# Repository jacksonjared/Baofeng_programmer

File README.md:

# Baofeng Programming Adapter

This board adapts the 5 volt USB port from a computer to 3V3 UART for use with programming Baofeng or similar chinese HTs. Most of these radios use a "Kenwood style" connector for programming; I have chosen to use separate 3.5mm and 2.5mm jacks as, annoyingly, several of the brands use non-standard spacing so as to make most cable incompatible. I have also elected to use a Silicon Labs chip to avoid the driver fiasco with the other common supplier of cheap UART bridge ICs.

## 3d

Within the folder labled '3d', you will find a .step file of the complete board and all its components, as well as models for the non-standard parts I used. I made a casing for this board to be 3D printed, but I currently do not have that file on hand. If I get a copy of it again sometime in the future, I will add it.

## gerber.zip

This is an archive of all the gerber files needed for manufacturing. I did not bother having this assembled in the factory so there is no BOM or pick-and-place file.

## main_board

I originally made this board in Kicad 5, and have since updated it to Kicad 6. I do not see anything obviously wrong with the project after converting, but I have not looked that close. If I notice any problems, I will fix them and push the change.

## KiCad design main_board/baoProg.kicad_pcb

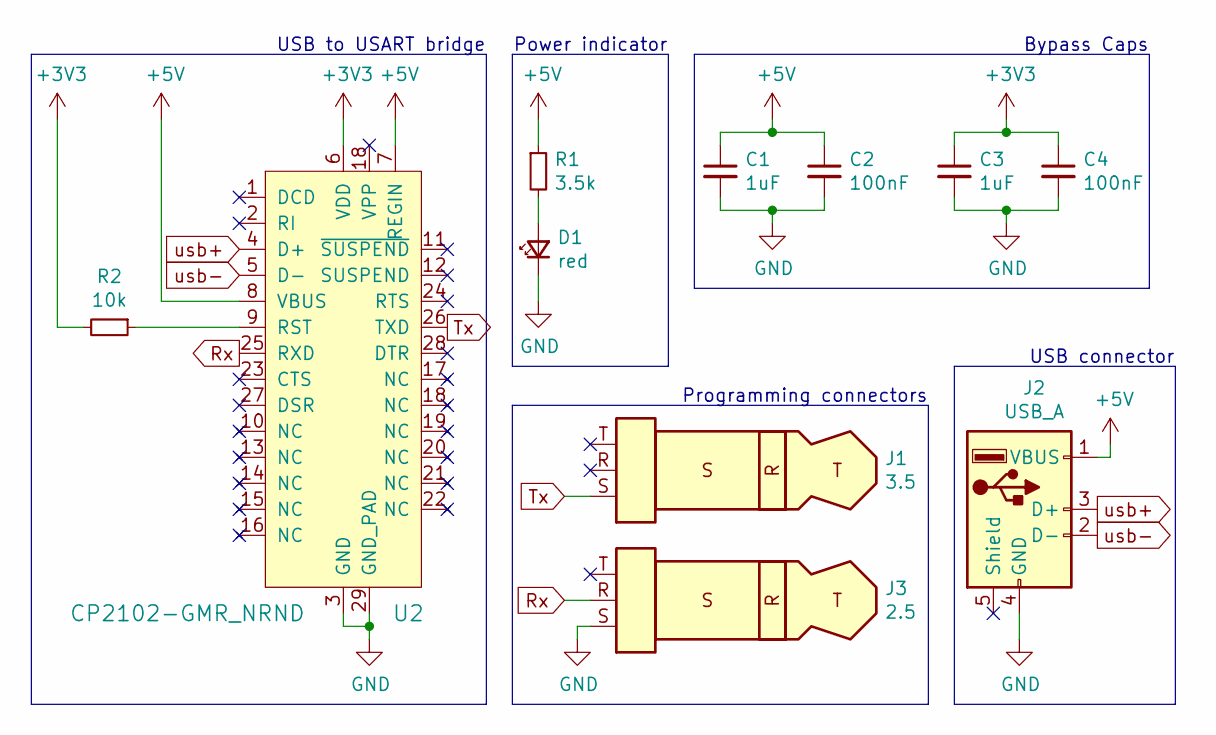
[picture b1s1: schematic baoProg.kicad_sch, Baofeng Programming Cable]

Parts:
C1, C3: 1uF; C_0603_1608Metric_Pad1.08x0.95mm_HandSolder
C2, C4: 100nF; C_0603_1608Metric_Pad1.08x0.95mm_HandSolder
D1: red; LED_0603_1608Metric_Castellated
J1: 3.5; STX-3000
J2: USB_A; USB_A_CNCTech_1001-011-01101_Horizontal_3d
J3: 2.5; STX-2000
R1: 3.5k; R_0805_2012Metric_Pad1.20x1.40mm_HandSolder
R2: 10k; R_0805_2012Metric_Pad1.20x1.40mm_HandSolder
U2: CP2102-GMR_NRND; QFN-28-1EP_5x5mm_P0.5mm_EP3.35x3.35mm_ThermalVias; MPN CP2102-GMR; Digi-Key_PN 336-1160-1-ND

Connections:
+3V3: C3.1, C4.1, R2.2, U2.6 (VDD)
+5V: C1.1, C2.1, J2.1 (VBUS), R1.1, U2.7 (REGIN), U2.8 (VBUS)
GND: C1.2, C2.2, C3.2, C4.2, D1.1 (K), J2.4 (GND), J3.S, U2.3 (GND), U2.29 (GND_PAD)
unnamed: D1.2 (A), R1.2
unnamed: R2.1, U2.9 (RST)
Rx: J3.R, U2.25 (RXD)
Tx: J1.S, U2.26 (TXD)
usb+: J2.3 (D+), U2.4 (D+)
usb-: J2.2 (D-), U2.5 (D-)

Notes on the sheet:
USB connector
Bypass Caps
Power indicator
USB to USART bridge
Programming connectors

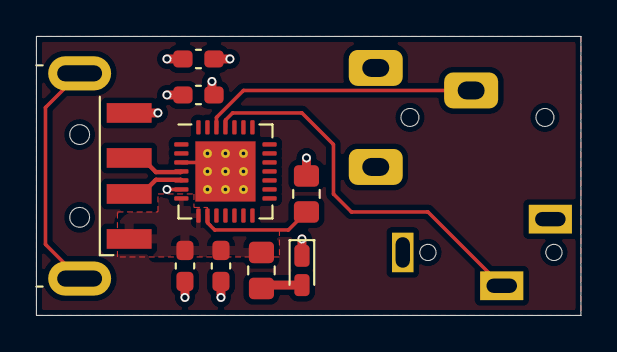
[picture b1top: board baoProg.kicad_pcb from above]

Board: 4 copper layers, 30.2 x 15.5 mm, 11 parts (0 on the bottom side), 9 nets.

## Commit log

2022-04-17 Intermediate
2022-04-17 Sync to current state
